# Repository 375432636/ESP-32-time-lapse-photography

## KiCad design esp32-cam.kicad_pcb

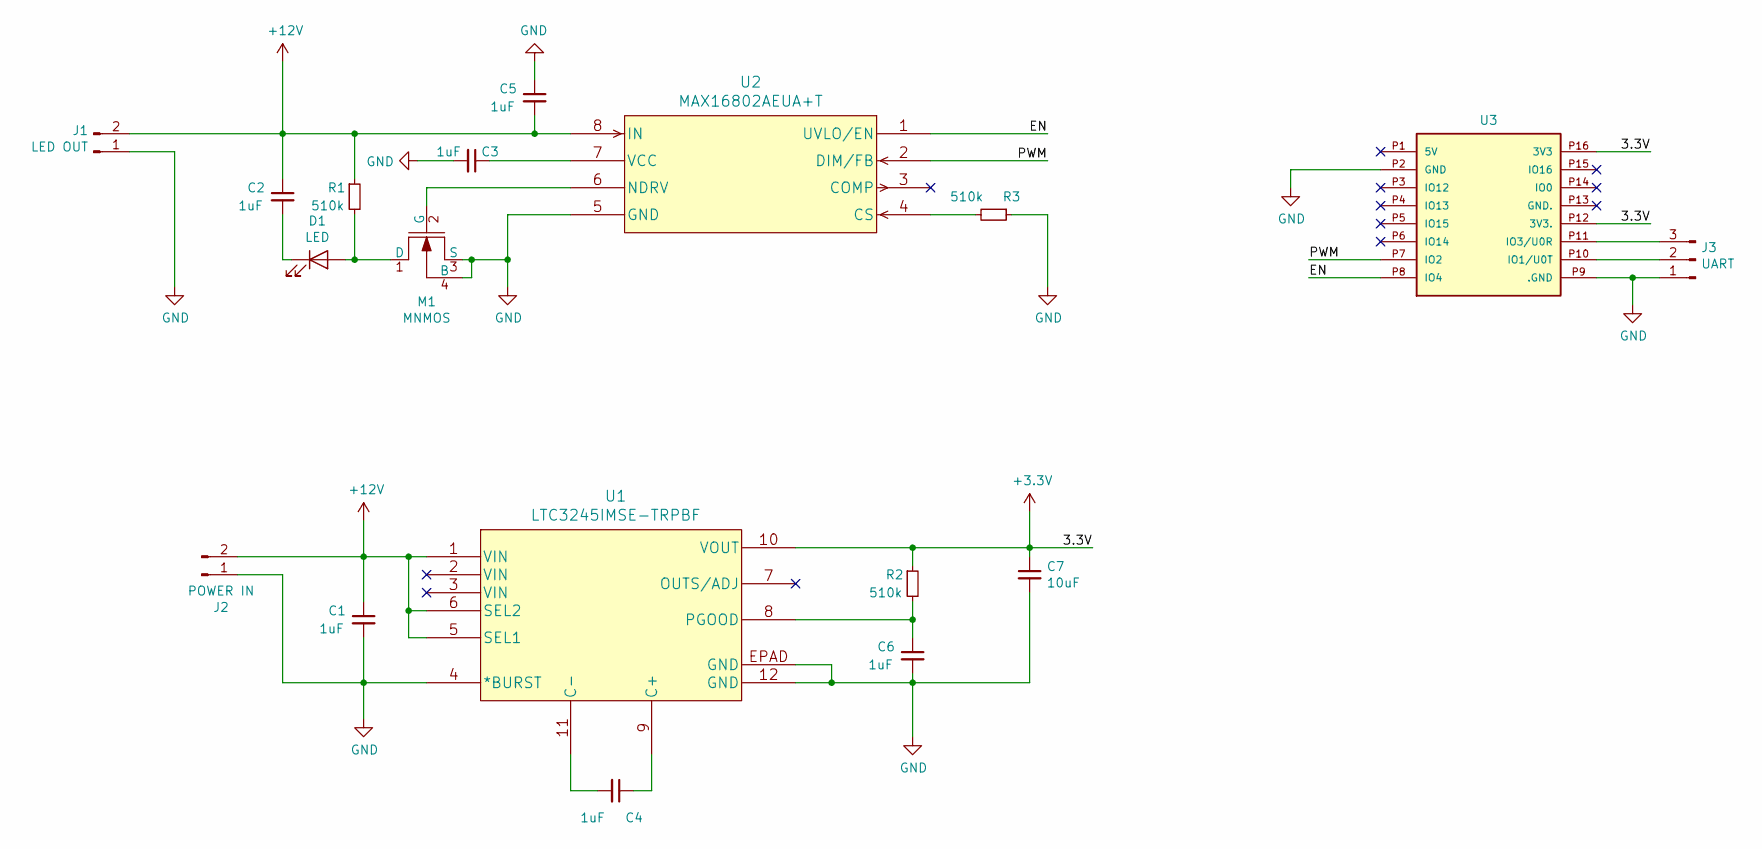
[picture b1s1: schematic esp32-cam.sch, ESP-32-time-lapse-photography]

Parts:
C1, C2, C3, C4, C5, C6: 1uF; C_0805_2012Metric_Pad1.15x1.40mm_HandSolder
C7: 10uF; C_0805_2012Metric_Pad1.15x1.40mm_HandSolder
D1: LED; LED_0805_2012Metric_Pad1.15x1.40mm_HandSolder
J1: LED OUT; PinHeader_1x02_P2.54mm_Vertical
J2: POWER IN; PinHeader_1x02_P2.54mm_Vertical
J3: UART; PinHeader_1x03_P2.54mm_Vertical
M1: MNMOS; TO-220-4_Horizontal_TabDown
R1, R2, R3: 510k; C_0805_2012Metric_Pad1.15x1.40mm_HandSolder
U1: LTC3245IMSE-TRPBF
U2: MAX16802AEUA+T; MAX16802AEUA&plus_T
U3: ESP32-CAM

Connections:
+3V3: C7.1, R2.1, U1.10 (VOUT), U3.P12 (3V3.), U3.P16 (3V3)
+12V: C1.1, C2.1, C5.2, J1.2, J2.2, R1.1, U1.1 (VIN), U1.5 (SEL1), U1.6 (SEL2), U2.8 (IN)
/EN: U2.1 (UVLO/EN), U3.P8 (IO4)
/PWM: U2.2 (DIM/FB), U3.P7 (IO2)
GND: C1.2, C3.2, C5.1, C6.2, C7.2, J1.1, J2.1, J3.1, M1.3 (S), M1.4 (B), R3.1, U1.4 (*BURST), U1.12 (GND), U1.EPAD (GND), U2.5 (GND), U3.P2 (GND), U3.P9 (.GND)
unnamed: C2.2, D1.1 (K)
unnamed: C3.1, U2.7 (VCC)
unnamed: C4.1, U1.9 (C+)
unnamed: C4.2, U1.11 (C-)
unnamed: C6.1, R2.2, U1.8 (PGOOD)
unnamed: D1.2 (A), M1.1 (D), R1.2
unnamed: J3.2, U3.P10 (IO1/U0T)
unnamed: J3.3, U3.P11 (IO3/U0R)
unnamed: M1.2 (G), U2.6 (NDRV)
unnamed: R3.2, U2.4 (CS)

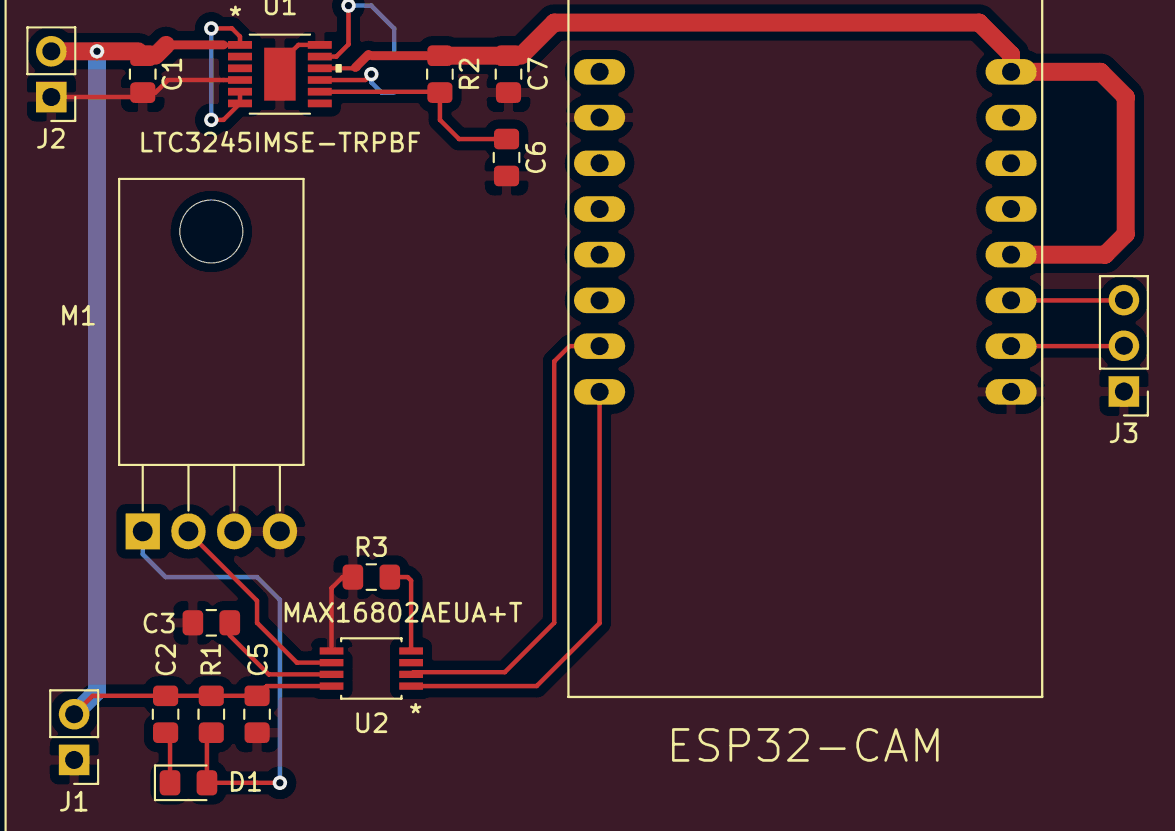
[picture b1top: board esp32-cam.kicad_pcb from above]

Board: 2 copper layers, 18 parts (1 on the bottom side), 15 nets.

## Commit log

2021-09-27 init

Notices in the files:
parts and their libraries:
Copyright 2021 Accelerated Designs. All rights reserved.
